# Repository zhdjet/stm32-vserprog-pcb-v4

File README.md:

# stm32-vserprog-pcb-v4
Improved pcb project based on dword1511's stm32-vserprog-pcb-v3 by KiCad.

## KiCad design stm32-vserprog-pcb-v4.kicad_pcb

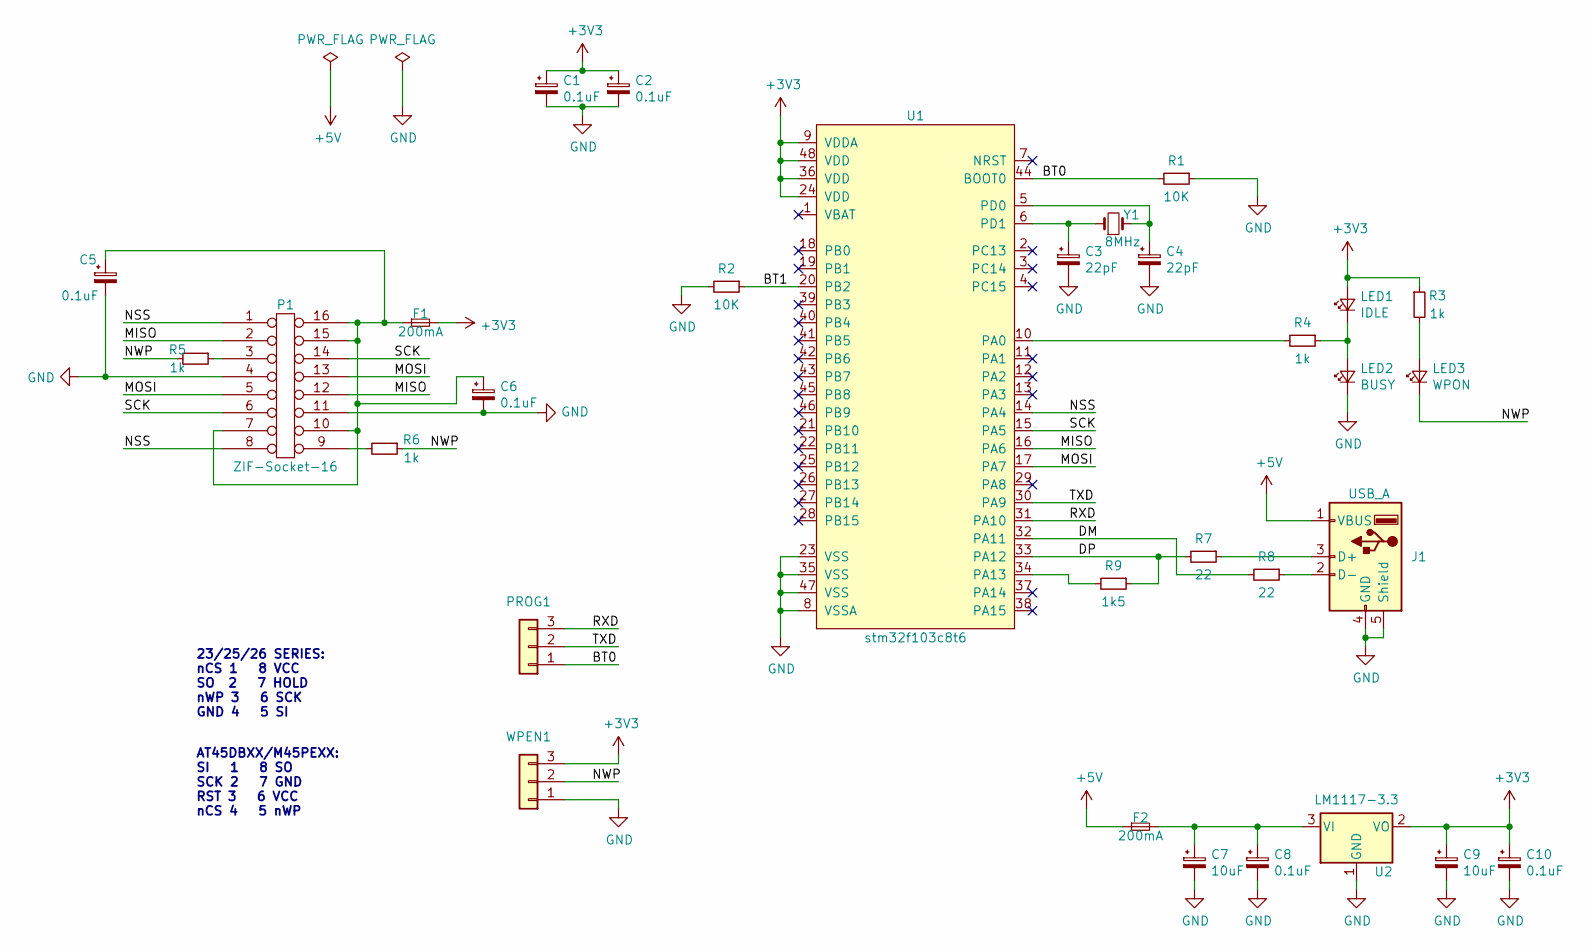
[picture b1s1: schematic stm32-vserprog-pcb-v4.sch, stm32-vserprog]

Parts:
C1, C2, C5, C6, C8, C10: 0.1uF; C_0805_2012Metric_Pad1.15x1.40mm_HandSolder
C3, C4: 22pF; C_0805_2012Metric_Pad1.15x1.40mm_HandSolder
C7, C9: 10uF; C_0805_2012Metric_Pad1.15x1.40mm_HandSolder
F1, F2: 200mA; Fuse_0805_2012Metric_Pad1.15x1.40mm_HandSolder
J1: USB_A; USB_A_CNCTech_1001-011-01101_Horizontal
LED1: IDLE; LED_0805_2012Metric_Pad1.15x1.40mm_HandSolder
LED2: BUSY; LED_0805_2012Metric_Pad1.15x1.40mm_HandSolder
LED3: WPON; LED_0805_2012Metric_Pad1.15x1.40mm_HandSolder
P1: ZIF-Socket-16; 216-3340
PROG1: PinHeader_1x03_P2.54mm_Vertical
R1, R2: 10K; R_0805_2012Metric_Pad1.15x1.40mm_HandSolder
R3, R4, R5, R6: 1k; R_0805_2012Metric_Pad1.15x1.40mm_HandSolder
R7, R8: 22; R_0805_2012Metric_Pad1.15x1.40mm_HandSolder
R9: 1k5; R_0805_2012Metric_Pad1.15x1.40mm_HandSolder
U1: stm32f103c8t6; LQFP-48_7x7mm_P0.5mm
U2: LM1117-3.3; SOT-223
WPEN1: PinHeader_1x03_P2.54mm_Vertical
Y1: 8MHz; Crystal_HC49-4H_Vertical

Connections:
+3V3: C1.1, C2.1, C9.1, C10.1, F1.2, LED1.2 (A), R3.1, U1.9 (VDDA), U1.24 (VDD), U1.36 (VDD), U1.48 (VDD), U2.2 (VO), WPEN1.3
+5V: F2.1, J1.1 (VBUS)
/BT0: PROG1.1, R1.2, U1.44 (BOOT0)
/BT1: R2.1, U1.20 (PB2)
/DM: R8.2, U1.32 (PA11)
/DP: R7.2, R9.1, U1.33 (PA12)
/MISO: P1.2, P1.12, U1.16 (PA6)
/MOSI: P1.5, P1.13, U1.17 (PA7)
/NSS: P1.1, P1.8, U1.14 (PA4)
/NWP: LED3.1 (K), R5.2, R6.1, WPEN1.2
/RXD: PROG1.3, U1.31 (PA10)
/SCK: P1.6, P1.14, U1.15 (PA5)
/TXD: PROG1.2, U1.30 (PA9)
GND: C1.2, C2.2, C3.2, C4.2, C5.2, C6.2, C7.2, C8.2, C9.2, C10.2, J1.4 (GND), J1.5 (Shield), LED2.1 (K), P1.4, P1.11, R1.1, R2.2, U1.8 (VSSA), U1.23 (VSS), U1.35 (VSS), U1.47 (VSS), U2.1 (GND), WPEN1.1
unnamed: C3.1, U1.6 (PD1), Y1.1
unnamed: C4.1, U1.5 (PD0), Y1.2
unnamed: C5.1, C6.1, F1.1, P1.7, P1.10, P1.15, P1.16
unnamed: C7.1, C8.1, F2.2, U2.3 (VI)
unnamed: J1.2 (D-), R8.1
unnamed: J1.3 (D+), R7.1
unnamed: LED1.1 (K), LED2.2 (A), R4.1
unnamed: LED3.2 (A), R3.2
unnamed: P1.3, R5.1
unnamed: P1.9, R6.2
unnamed: R4.2, U1.10 (PA0)
unnamed: R9.2, U1.34 (PA13)

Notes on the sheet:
23/25/26 SERIES: nCS 1 8 VCC SO 2 7 HOLD nWP 3 6 SCK GND 4 5 SI
AT45DBXX/M45PEXX: SI 1 8 SO SCK 2 7 GND RST 3 6 VCC nCS 4 5 nWP

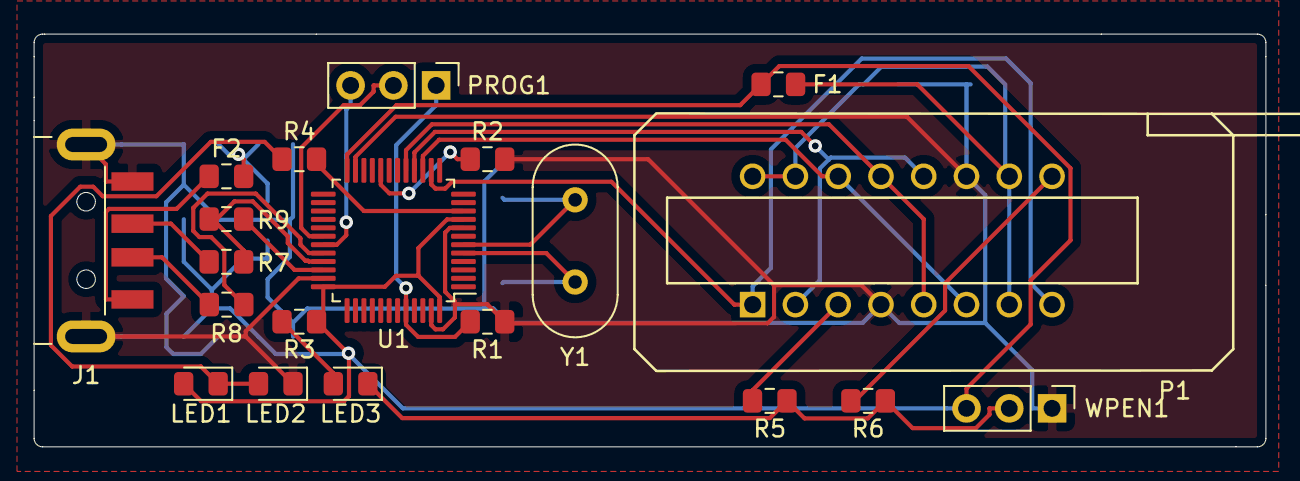
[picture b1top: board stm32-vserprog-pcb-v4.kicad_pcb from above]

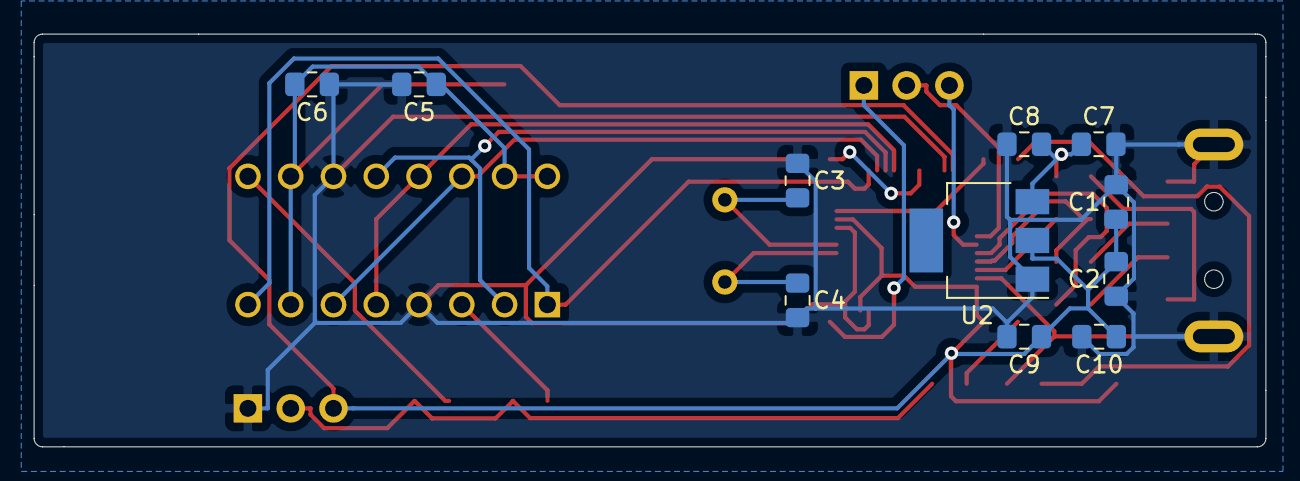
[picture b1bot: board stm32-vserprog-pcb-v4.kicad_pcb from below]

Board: 2 copper layers, 73.2 x 24.5 mm, 31 parts (11 on the bottom side), 26 nets.

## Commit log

2019-10-07 completion file
